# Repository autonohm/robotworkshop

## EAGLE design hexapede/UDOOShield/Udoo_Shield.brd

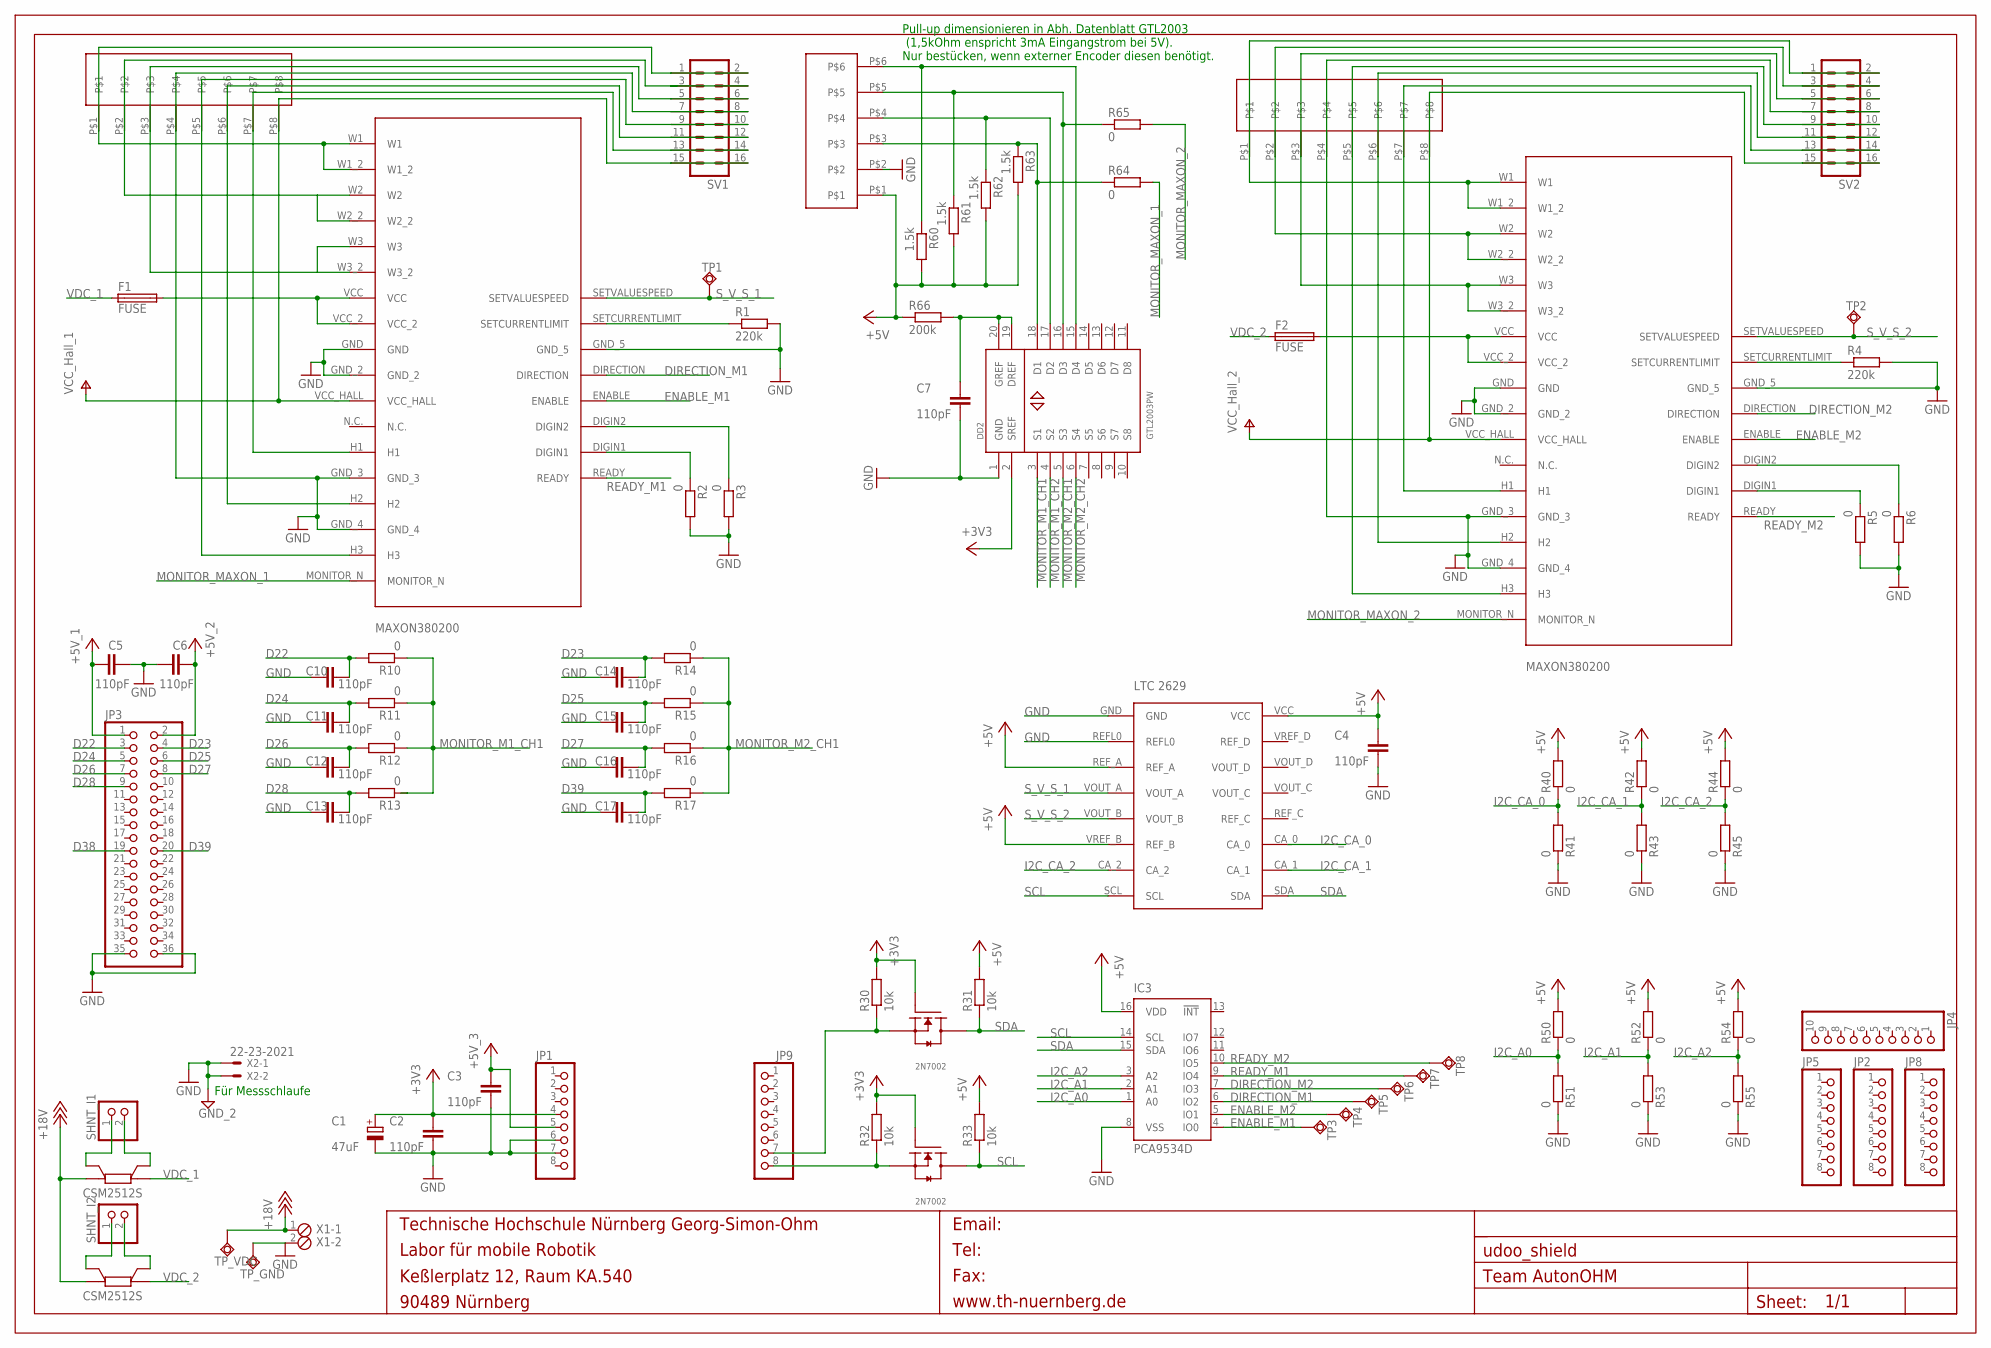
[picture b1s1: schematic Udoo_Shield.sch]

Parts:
C1: 47uF; PANASONIC_F
C2, C3, C4, C5, C6, C7, C10, C11, C12, C13, C14, C15, C16, C17: 110pF; SMD-0805
DD2: GTL2003PW; TSSOP20
ENCODER: WAGO_PICOMAX_35_6POLIG
F1, F2: FUSE
FRAME1: A3L-LOC
IC3: PCA9534D; SO16W
JP1, JP2, JP5, JP8, JP9: PINHD-1X8; 1X08
JP3: PINHD-2X18; 2X18
JP4: PINHD-1X10; 1X10
R1, R4: 220k; M1206
R2, R3, R5, R6, R10, R11, R12, R13, R14, R15, R16, R17, R40, R41, R42, R43, R44, R45, R50, R51, R52, R53, R54, R55, R64, R65: 0; M0805
R30, R31, R32, R33: 10k; M0805
R60, R61, R62, R63: 1.5k; M0805
R66: 200k; M0805
SHNT_I1, SHNT_I2: PINHD-1X2; 1X02
SV1, SV2: MA08-2
TP1, TP2, TP3, TP4, TP5, TP6, TP7, TP8: TPSQB1,27; B1,27
TP_GND: TPSQB1,27; B1,27
TP_VDC: TPSQB1,27; B1,27
U$1, U$2: MAXON380200; 380200
U$3, U$4: WAGO_PICOMAX_35_8POLIG
U$5: LTC2629
U$6, U$15: N-CH_MOSFET_2N7002; 2N7002
U$10, U$14: CSM2512S
X1: MPT2; 2POL254
X2: 22-23-2021

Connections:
+3V3: C1.+, C2.1, DD2.2 (SREF), JP1.4, R30.2, R32.2, U$6.GATE (G), U$15.GATE (G)
+5V: C3.1, C4.1, C5.1, C6.2, ENCODER.P$1, IC3.16 (VDD), JP1.5, JP3.1, JP3.2, R31.2, R33.2, R40.2, R42.2, R44.2, R50.2, R52.2, R54.2, R60.2, R61.2, R62.2, R63.2, R66.1, U$5.REF_A, U$5.VCC, U$5.VREF_B (REF_B)
+18V: TP_VDC.TP, U$10.I_2, U$14.I_2, X1.1
D1: JP9.8, R32.1, U$6.SOURCE (S)
D22: C10.2, JP3.3, R10.2
D23: C14.2, JP3.4, R14.2
D24: C11.2, JP3.5, R11.2
D25: C15.2, JP3.6, R15.2
D26: C12.2, JP3.7, R12.2
D27: C16.2, JP3.8, R16.2
D28: C13.2, JP3.9, R13.2
D34: JP9.7, R30.1, U$15.SOURCE (S)
D38: JP3.19
D39: C17.2, JP3.20, R17.2
DIRECTION_M1: IC3.6 (IO2), TP5.TP, U$1.DIRECTION
DIRECTION_M2: IC3.7 (IO3), TP6.TP, U$2.DIRECTION
ENABLE_M1: IC3.4 (IO0), TP3.TP, U$1.ENABLE
ENABLE_M2: IC3.5 (IO1), TP4.TP, U$2.ENABLE
GND: C1.-, C2.2, C3.2, C4.2, C5.2, C6.1, C7.2, C10.1, C11.1, C12.1, C13.1, C14.1, C15.1, C16.1, C17.1, DD2.1 (GND), ENCODER.P$2, IC3.8 (VSS), JP1.6, JP1.7, JP3.35, JP3.36, R1.2, R2.2, R3.2, R4.2, R5.2, R6.2, R41.1, R43.1, R45.1, R51.1, R53.1, R55.1, SV1.7, SV1.8, SV2.7, SV2.8, TP_GND.TP, U$1.GND, U$1.GND_2, U$1.GND_3, U$1.GND_4, U$1.GND_5, U$2.GND, U$2.GND_2, U$2.GND_3, U$2.GND_4, U$2.GND_5, U$3.P$4, U$4.P$4, U$5.GND, U$5.REFL0, X1.2, X2.1, X2.2
I2C_A0: IC3.1 (A0), R50.1, R51.2
I2C_A1: IC3.2 (A1), R52.1, R53.2
I2C_A2: IC3.3 (A2), R54.1, R55.2
I2C_CA_0: R40.1, R41.2, U$5.CA_0
I2C_CA_1: R42.1, R43.2, U$5.CA_1
I2C_CA_2: R44.1, R45.2, U$5.CA_2
MONITOR_M1_CH1: DD2.3 (S1), R10.1, R11.1, R12.1, R13.1
MONITOR_M1_CH2: DD2.4 (S2)
MONITOR_M2_CH1: DD2.5 (S3), R14.1, R15.1, R16.1, R17.1
MONITOR_M2_CH2: DD2.6 (S4)
MONITOR_MAXON_1: R64.2, U$1.MONITOR_N
MONITOR_MAXON_2: R65.2, U$2.MONITOR_N
unnamed: SV2.1, SV2.2, U$2.W1, U$2.W1_2, U$3.P$1
unnamed: SV2.3, SV2.4, U$2.W2, U$2.W2_2, U$3.P$2
unnamed: SV2.5, SV2.6, U$2.W3, U$2.W3_2, U$3.P$3
unnamed: F1.P$2 (2), U$1.VCC, U$1.VCC_2
unnamed: SHNT_I2.1, U$14.E_2
unnamed: R1.1, U$1.SETCURRENTLIMIT
unnamed: SV2.13, SV2.14, U$2.H1, U$3.P$7
unnamed: SV1.13, SV1.14, U$1.H1, U$4.P$7
unnamed: SV2.11, SV2.12, U$2.H2, U$3.P$6
unnamed: SV2.9, SV2.10, U$2.H3, U$3.P$5
unnamed: F2.P$2 (2), U$2.VCC, U$2.VCC_2
unnamed: R4.1, U$2.SETCURRENTLIMIT
unnamed: SV1.11, SV1.12, U$1.H2, U$4.P$6
unnamed: SV1.9, SV1.10, U$1.H3, U$4.P$5
unnamed: SV1.1, SV1.2, U$1.W1, U$1.W1_2, U$4.P$1
unnamed: SHNT_I1.1, U$10.E_2
unnamed: SHNT_I1.2, U$10.E_1
unnamed: SHNT_I2.2, U$14.E_1
unnamed: C7.1, DD2.19 (DREF), DD2.20 (GREF), R66.2
unnamed: DD2.18 (D1), ENCODER.P$3, R63.1, R64.1
unnamed: DD2.17 (D2), ENCODER.P$4, R62.1
unnamed: DD2.16 (D3), ENCODER.P$5, R61.1, R65.1
unnamed: R5.1, U$2.DIGIN1
unnamed: DD2.15 (D4), ENCODER.P$6, R60.1
unnamed: SV1.5, SV1.6, U$1.W3, U$1.W3_2, U$4.P$3
unnamed: R6.1, U$2.DIGIN2
unnamed: SV1.3, SV1.4, U$1.W2, U$1.W2_2, U$4.P$2
unnamed: R2.1, U$1.DIGIN1
unnamed: R3.1, U$1.DIGIN2
READY_M1: IC3.9 (IO4), TP7.TP, U$1.READY
READY_M2: IC3.10 (IO5), TP8.TP, U$2.READY
SCL: IC3.14 (SCL), R33.1, U$5.SCL, U$6.DRAIN (D)
SDA: IC3.15 (SDA), R31.1, U$5.SDA, U$15.DRAIN (D)
S_V_S_1: TP1.TP, U$1.SETVALUESPEED, U$5.VOUT_A
S_V_S_2: TP2.TP, U$2.SETVALUESPEED, U$5.VOUT_B
VDC_1: F1.P$1 (1), U$10.I_1
VDC_2: F2.P$1 (1), U$14.I_1
V_HALL_1: SV1.15, SV1.16, U$1.VCC_HALL, U$4.P$8
V_HALL_2: SV2.15, SV2.16, U$2.VCC_HALL, U$3.P$8

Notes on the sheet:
Pull-up dimensionieren in Abh. Datenblatt GTL2003 (1,5kOhm enspricht 3mA Eingangstrom bei 5V). Nur bestücken, wenn externer Encoder diesen benötigt.
Für Messschlaufe

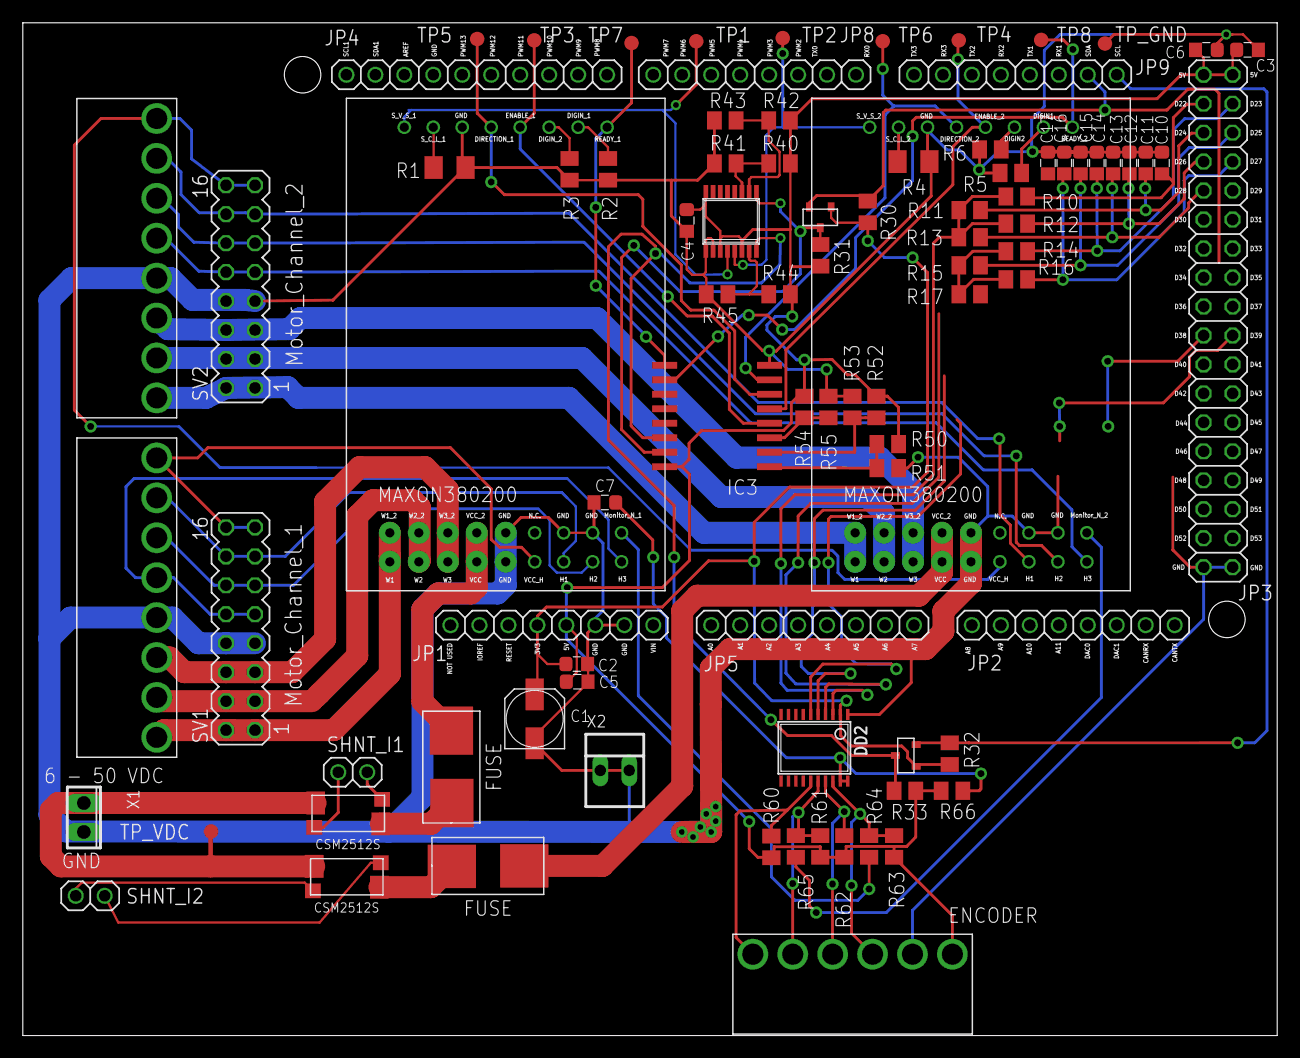
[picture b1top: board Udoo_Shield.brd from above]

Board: 2 copper layers, 110.0 x 88.8 mm, 90 parts (1 on the bottom side), 67 nets.

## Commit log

2015-09-08 added - first firmware version - old ohm_joyToVel package - two bare examples
2015-09-10 fixed bug for 2-channel control
2015-09-11 cleaned code of bare examples
2015-09-11 added CoDeSys example project for FRDM motor control
2015-09-30 added segger jlink bootloader
2015-09-30 added Readme
2015-10-01 final project meeting
2015-10-08 added Euler parameters
2015-10-08 added Euler parameters to firmware added float parameter transmission
2015-10-08 CoDeSys project archive with reduced cycle time adapted protocol with float parameters
2015-10-10 added methods for tf <-> pid conversion added documenting comments proved correctness of interfaces
2015-10-11 moved to CoDeSys V3.5.7 (did not fix the bug observed in CoDeSys Application: crash after long running motor control)
2015-10-12 added bootloader
2015-10-14 - Downgrade to CoDeSys version 3.5.6 - fixed communication issues - extended protocol (short and float distinction)
2015-10-14 added CODESYS_Control package for Raspberry
2015-10-18 added state control
2015-10-27 branch created
2015-10-27 added binary files (git annex)
2015-10-27 removed annex
2015-10-27 added motor shield firmware binary
2015-10-27 added binary files
2015-10-27 fixed tiny bug in CoDeSys project
2015-11-04 -- initial commit for easy to use joy2vel_ps3_node -- tested with ps3 game pad wired
2016-02-03 -- moved studierbot nodes from ohm_robots to this repository
2016-02-03 -- added missing package for cleanUp2016
2016-02-15 -- initial commit for tutorials
2016-02-15 -- clean upd of repo
2016-02-15 -- added matlab data
2016-02-15 -- added sumodule for ros tutorials
2016-03-19 revised directory structure
2016-03-23 added pi cam tarball
2016-03-30 Translate comments to english
2016-04-19 -- added metha packages
2016-04-19 -- modifications for new structure
2016-04-19 -- modificatons for meta packages
2016-04-19 -- renamed hexapete -> hexapede -- added new folder for launch files in hexapede
2016-04-19 -- minor changes in header of package.xml
2016-04-23 added electronic layout for Maxon Interface
2016-05-09 added firmware for hexapede
2016-05-09 renamed hexapete... -> hexapede...
2016-05-11 renamed hexapete -> hexapede
2016-05-11 development version
2016-06-21 fixed protocol problems (wrong interpretation of cr, lf)
2016-06-21 moved binaries to lfs
2016-07-11 Update for motor firmware (fixed encoder read out)
2017-04-28 extension for new motorcontroller (four channel support)
2017-05-22 added nodes for tank chassis
2017-05-22 added missing file
2017-06-02 New firmware for 6-channel MC
2017-06-06 minor changes (source code layout)
2017-06-08 test version for tank chassis node
2017-07-04 increased pwm frequency of firmware
2017-09-21 minor change
2017-09-28 added Lego tutorials (6WD robot)
2017-10-08 added template for mechanum basis
2017-10-11 working implementation for mechanum concept
2017-11-02 fixed: wrong output of input value in step_response_closed_loop.cpp
2017-11-12 added comments
2017-11-13 removed obsolete (duplicated) file
2017-12-05 Added tutorial for C++ state machine implementation
2017-12-09 generalized interface of motor controller
2017-12-10 added launch file parameters to assign channels and PID parameters
2017-12-10 unified motor/robot interfaces
2017-12-11 fixed launch file type
2017-12-11 generalized interfaces, fixed meta package dependencies
2017-12-11 fixed wrong gear ratio
2017-12-14 minor change: typo
2017-12-19 Added preprocessing software for ATMEL TINY13
2018-01-15 fixed bugs in skid steering concept
2018-01-16 Added udev rules
2018-01-16 Adaptation to new udev rules
2018-02-22 added usage of new commands for novel motor controller design
2018-04-03 development version (initial commit for CAN interface)
2018-05-09 added matlab templates for kinematics tutorial
2018-05-09 added matlab templates for kinematics intro
2018-05-13 added threaded interface
2018-05-13 bugfix for rotational speed determination
2018-06-05 fixed documentation, adapted CAN node for mechanum drive
2018-06-29 added new methods for CAN interface (max PwM, frequency scale)
2018-07-10 added new features (pos mode) fixed CAN connection interrupt
2018-10-05 added sync method to reset timer on multiple controllers
2018-10-23 new version based on CAN interface (skid steering tested)
2018-10-23 test version for mechanum and skid steering kinematics
2018-10-24 cleand code, added sync signal
2018-10-25 added udev rules, modified up/down scripts
2018-11-05 Added automatic pkill scland ACTION when USBtin is removed to its udev rule
2018-12-02 added class for add-on shield
2018-12-06 test version for robocup chassis
2018-12-07 fixed missing init call for socket listener
2019-03-12 adapted to new firware for new Evo DCDC converter
2019-03-12 added QT example for Evo DCDC converter
2019-03-12 replaced ifconfig (deprecated) with ip command
2019-04-25 fixed minor issue (compilation error with addon board)
2019-07-31 cleaned up
2019-07-31 added class and component diagrams
2019-07-31 added diagrams and online documentation
2019-07-31 adjusted class diagram
2019-07-31 minor changes
2019-07-31 removed obsolete file
2019-08-01 added documentation for starting robots up
2019-08-01 removed uvc package
2019-08-01 added interface to activate/deactivate anti windup functionality
2019-08-04 added documentation
2019-08-04 fixed broken diagram
2019-08-08 rearranged repository
2019-09-12 added IMU test application
2019-12-08 added encoder polarity invert option
2019-12-08 Working test version
2020-03-16 Add code for disabling front wheel only drive
2020-03-16 Add missing vars for joystick buttons
2020-03-16 Remove light trigger function
2020-03-16 Add rearWheelsOnly button option
2020-03-16 Fix rearWheelsOnly & frontWheelsOnly
2020-03-16 Set c++ version correctly and set to c++14
2020-03-16 Chang type of _fireButton to bool in SkidSteering.h
2020-03-16 Add buttonReleased function in skid_steering
2020-03-16 Print info when front or rear wheels only get activated
2020-03-16 Add _fireButton mapping back again
2021-08-03 Modify udev rule for USBtin USB to CAN converter and add systemd service so that on plugging in the slcan0 interface gets set up automatically and stopped when plugged out.
2021-08-04 Fix slcand.service on old ubuntu version by calling ExecPostStart with full PATH
2021-11-08 added publisher for rpm
